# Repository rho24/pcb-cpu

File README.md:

# pcb-cpu

Project to create a cpu across multiple pcbs.

## Thoughts
* Risc-v inspired
* 16bit

## Useful links
* https://rv8.io/isa.html
* https://www.mouser.co.uk/datasheet/2/302/PCA9698-1127696.pdf

## Instructions
* Reg     - Load Immediate
* ALU ops - ADD, SUB, SHIFT L/R, AND, OR, XOR, Set Compare
* Mem ops - Load mem, Store mem
* PC ops  - Branch equal, Branch not equal, Jump, Jump Offset, Jump and Link, Jump and Link Offset, Ret

## Registries
* x0 - Zero
* x1 - Return address
* x2 - Stack pointer
* x3 - Function arg/return/temp
* x4 - Function arg/return/temp
* x5 - Function arg/temp
* x6 - Function arg/temp
* x7 - temp

## Instruction formats
                    F E D C B A 9 8 7 6 5 4 3 2 1 0
Load Imm            Imm-----------------Rd----Opcode
ALU                 Ra----Rb----  Func--Rd----Opcode
Mem                 Ra----Rofset        Rd----Opcode
Branch              Ra----Rofset        Rd----Opcode
Jump                Imm-----------------Rd----Opcode
Jump Offset         Imm-----------------Rd----Opcode
Jump Reg            Ra----              Rd----Opcode

## Signals
Ra      16
Rb      16
Rd      16
Raa     5
Rba     5
Rda     5
Rare    1
Rbre    1
Rdwr    1
        66

Busd    16
Busa    16
Busre   1
Buswr   1
        34

Aluoe   1
Alufunc 4
        5

        105

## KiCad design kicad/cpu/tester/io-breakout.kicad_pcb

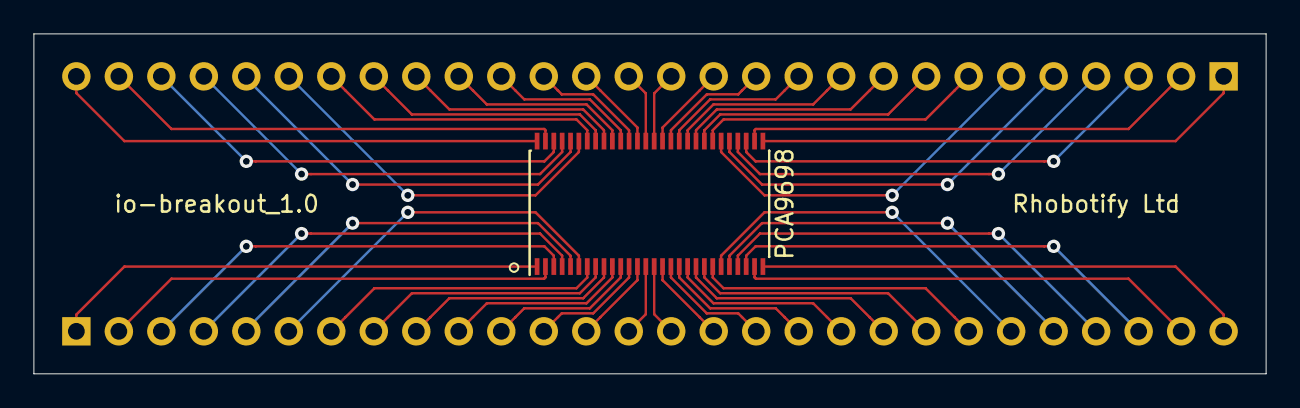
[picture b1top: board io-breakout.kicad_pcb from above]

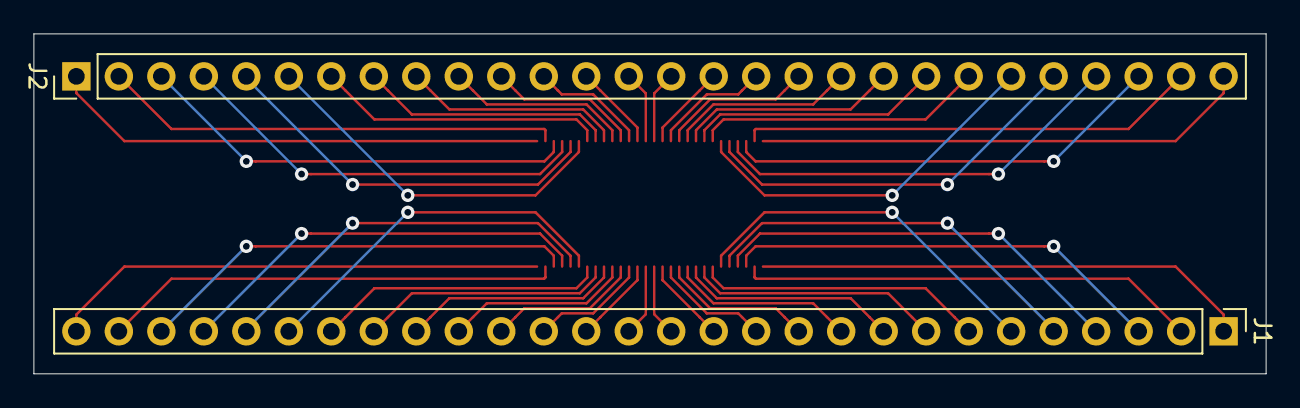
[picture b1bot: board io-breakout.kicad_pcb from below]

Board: 2 copper layers, 73.7 x 20.3 mm, 3 parts (2 on the bottom side), 56 nets.

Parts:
J1, J2: Conn_01x28_Male; PinHeader_1x28_P2.54mm_Vertical
U1: PCA9698; TSSOP-56_6.1x14mm_P0.5mm

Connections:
unnamed: J1.1, U1.1
unnamed: J1.2, U1.2
unnamed: J1.3, U1.3
unnamed: J1.4, U1.4
unnamed: J1.5, U1.5
unnamed: J1.6, U1.6
unnamed: J1.7, U1.7
unnamed: J1.8, U1.8
unnamed: J1.9, U1.9
unnamed: J1.10, U1.10
unnamed: J1.11, U1.11
unnamed: J1.12, U1.12
unnamed: J1.13, U1.13
unnamed: J1.14, U1.14
unnamed: J1.15, U1.15
unnamed: J1.16, U1.16
unnamed: J1.17, U1.17
unnamed: J1.18, U1.18
unnamed: J1.19, U1.19
unnamed: J1.20, U1.20
unnamed: J1.21, U1.21
unnamed: J1.22, U1.22
unnamed: J1.23, U1.23
unnamed: J1.24, U1.24
unnamed: J1.25, U1.25
unnamed: J1.26, U1.26
unnamed: J1.27, U1.27
unnamed: J1.28, U1.28
unnamed: J2.1, U1.29
unnamed: J2.2, U1.30
unnamed: J2.3, U1.31
unnamed: J2.4, U1.32
unnamed: J2.5, U1.33
unnamed: J2.6, U1.34
unnamed: J2.7, U1.35
unnamed: J2.8, U1.36
unnamed: J2.9, U1.37
unnamed: J2.10, U1.38
unnamed: J2.11, U1.39
unnamed: J2.12, U1.40
unnamed: J2.13, U1.41
unnamed: J2.14, U1.42
unnamed: J2.15, U1.43
unnamed: J2.16, U1.44
unnamed: J2.17, U1.45
unnamed: J2.18, U1.46
unnamed: J2.19, U1.47
unnamed: J2.20, U1.48
unnamed: J2.21, U1.49
unnamed: J2.22, U1.50
unnamed: J2.23, U1.51
unnamed: J2.24, U1.52
unnamed: J2.25, U1.53
unnamed: J2.26, U1.54
unnamed: J2.27, U1.55
unnamed: J2.28, U1.56

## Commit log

2019-11-03 Beginnings
2019-11-06 Start f#
2019-11-07 More instructions
2019-11-09 Signals
2019-11-09 Add instructions
2019-11-09 Begin linker
2019-11-11 Linking
2019-11-11 Linked program runs
2019-11-14 Start verilog
2019-11-15 more formal
2019-11-16 Links
2019-11-16 Wired
2019-11-16 Add plot files
2019-11-17 Get tb working
2019-11-17 Add memory
2019-11-17 Fix mem file
2019-11-17 Add alu
2019-11-17 Starting control
2019-11-17 Get some instructions working
2019-11-23 More progress
2019-12-01 First blink
2019-12-01 Blinking
2019-12-01 Readme
2019-12-01 Not working yet
